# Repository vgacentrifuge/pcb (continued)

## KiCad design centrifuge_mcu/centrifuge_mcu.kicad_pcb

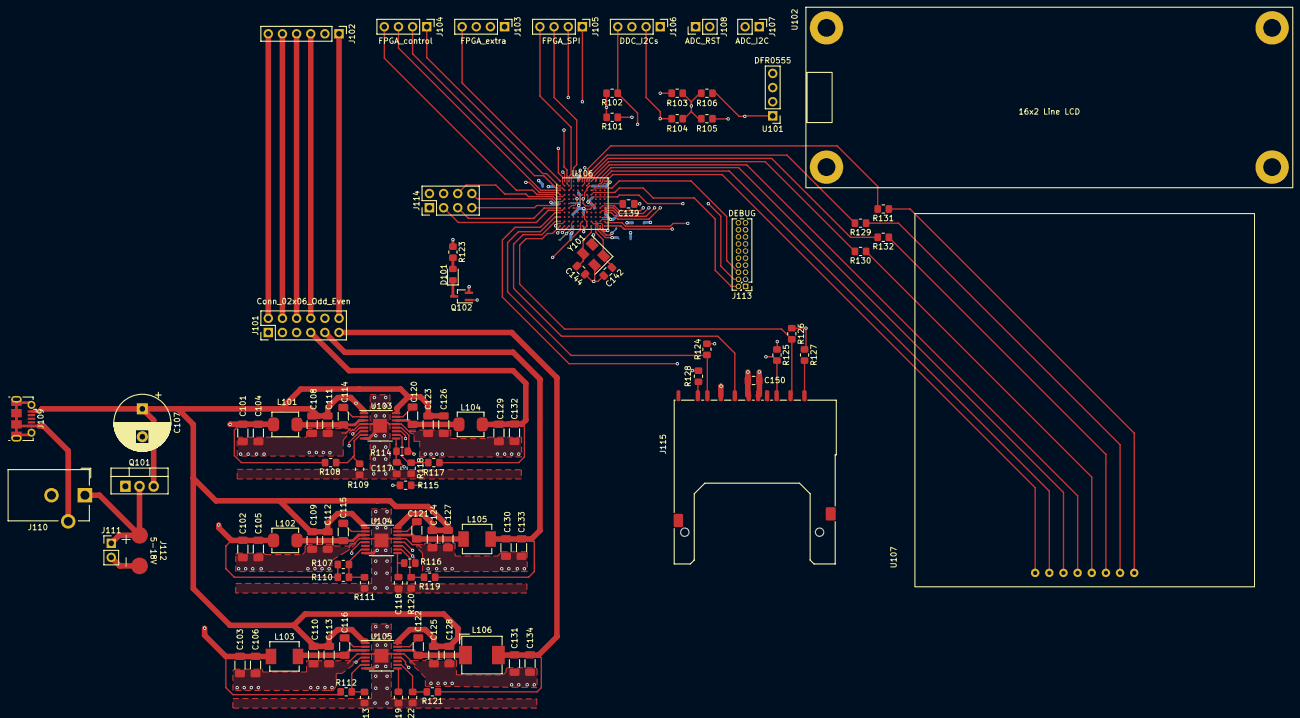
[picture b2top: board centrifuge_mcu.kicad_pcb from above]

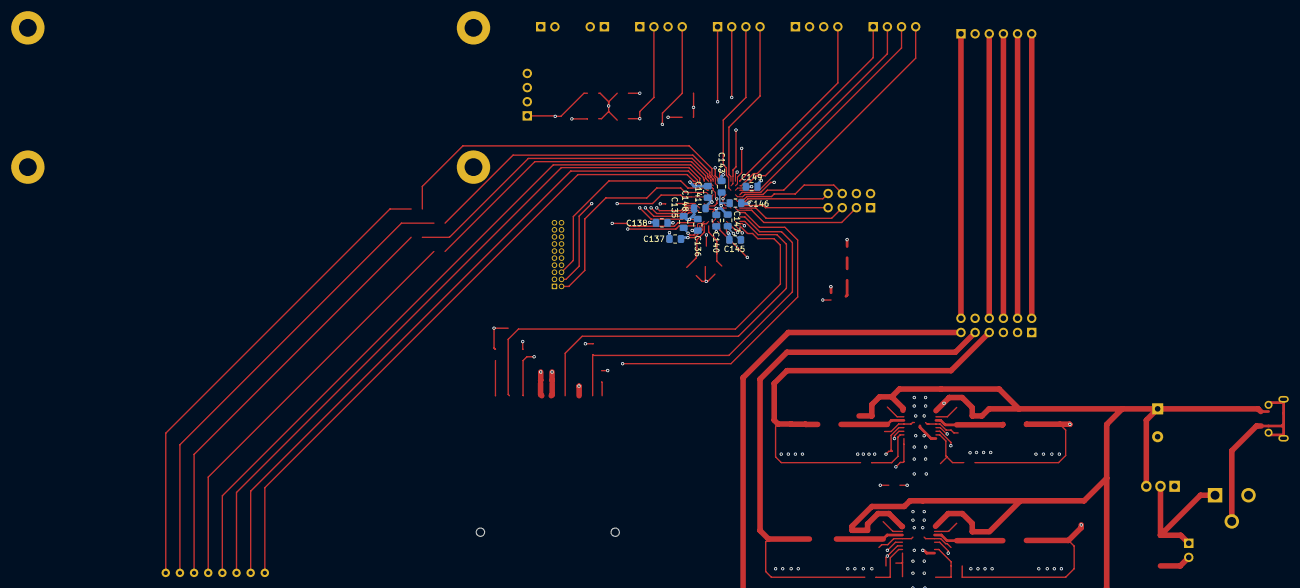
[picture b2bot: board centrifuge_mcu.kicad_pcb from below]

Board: 6 copper layers, 114 parts (12 on the bottom side), 94 nets.

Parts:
C101, C102, C103, C104, C105, C106, C129, C130, C131, C132, C133, C134: 22u; C_1206_3216Metric_Pad1.33x1.80mm_HandSolder
C107: 100u; CP_Radial_D10.0mm_P5.00mm
C108, C109, C110, C123, C124, C125: 10u; C_1206_3216Metric_Pad1.33x1.80mm_HandSolder
C111, C112, C113, C114, C115, C116, C120, C121, C122, C126, C127, C128: 100n; C_1206_3216Metric_Pad1.33x1.80mm_HandSolder
C117, C118, C119, C139: 1u; C_0805_2012Metric_Pad1.18x1.45mm_HandSolder
C135, C136, C137, C140, C141, C143, C145, C146, C147, C148, C150: 100n; C_0805_2012Metric_Pad1.18x1.45mm_HandSolder
C138, C149: 10u; C_0805_2012Metric_Pad1.18x1.45mm_HandSolder
C142, C144: 12p; C_0805_2012Metric_Pad1.18x1.45mm_HandSolder
D101: LED_YELLOW_2V_20mA; D_0805_2012Metric_Pad1.15x1.40mm_HandSolder
J101: Conn_02x06_Odd_Even; PinHeader_2x06_P2.54mm_Vertical
J102: FPGA_Power; PinHeader_1x06_P2.54mm_Vertical
J103: FPGA_extra; PinHeader_1x04_P2.54mm_Vertical
J104: FPGA_control; PinHeader_1x04_P2.54mm_Vertical
J105: FPGA_SPI; PinHeader_1x04_P2.54mm_Vertical
J106: DDC_I2Cs; PinHeader_1x04_P2.54mm_Vertical
J107: ADC_I2C; PinHeader_1x02_P2.54mm_Vertical
J108: ADC_RST; PinHeader_1x02_P2.54mm_Vertical
J109: USB_B_Micro; USB_Micro-B_Molex-105017-0001
J110: Barrel_Jack; BarrelJack_CUI_PJ-102AH_Horizontal
J111: PowerIn; PinHeader_1x02_P2.54mm_Vertical
J112: PowerPads
J113: DEBUG; PinHeader_2x10_P1.27mm_Vertical
J114: Extra MCU GPIO; PinHeader_2x04_P2.54mm_Vertical
J115: SD_Card; SD_Kyocera_145638009511859+
L101, L102, L104: 1.5u; L_Sumida_CR75
L103, L105: 2.2u; L_Vishay_IHLP-2020
L106: 3.3u; L_TDK_7065
Q101: Q_PMOS_DGS; TO-220-3_Vertical
Q102: Q_NMOS_GSD; SOT-323_SC-70_Handsoldering
R101, R102, R103, R104, R105, R106: 2.2k; R_0805_2012Metric_Pad1.20x1.40mm_HandSolder
R107: 5.6M; R_0805_2012Metric_Pad1.20x1.40mm_HandSolder
R108: 6.81k; R_0805_2012Metric_Pad1.20x1.40mm_HandSolder
R109, R111, R113, R118, R120, R122: 22.1k; R_0805_2012Metric_Pad1.20x1.40mm_HandSolder
R110: 33k; R_0805_2012Metric_Pad1.20x1.40mm_HandSolder
R112, R119: 73.2k; R_0805_2012Metric_Pad1.20x1.40mm_HandSolder
R114, R115, R116, R124, R125, R126, R127, R128, R129, R130, R131, R132: 10k; R_0805_2012Metric_Pad1.20x1.40mm_HandSolder
R117: 30.1k; R_0805_2012Metric_Pad1.20x1.40mm_HandSolder
R121: 124k; R_0805_2012Metric_Pad1.20x1.40mm_HandSolder
R123: 62; R_0805_2012Metric_Pad1.20x1.40mm_HandSolder
U101: DFR0555; PinHeader_1x04_P2.54mm_Vertical
U102: LCD16x2L; DFR0555
U103, U104, U105: TPS54294; TSSOP-16-1EP_4.4x5mm_P0.65mm_EP3x3mm_ThermalVias_EXTRA
U106: EFM32GG990F1024; BGA-112_9.0x9.0mm_Layout11x11_P0.8mm_Ball0.4mm_Pad0.35mm_NS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
U107: 4x4_keyboard; Adafruit 3844
Y101: VXM7-1366-48M0000000; Crystal_SMD_TXC_7M-4Pin_3.2x2.5mm_TIGHT

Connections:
+1V0: J101.6, J102.4
+1V8: J101.8, J102.3
+1V9: J101.4, J102.5
+3.3V: C135.1, C136.1, C137.1, C138.1, C140.1, C141.1, C143.1, C145.1, C146.1, C147.1, C148.1, C149.1, C150.2, J101.10, J102.2, J113.1, J114.1, J115.4 (VDD), R101.2, R102.2, R103.2, R104.2, R105.1, R106.1, R123.1, R124.2, R125.1, R126.1, R127.1, R128.2, U101.4 (VCC), U106.D5 (IOVDD_6), U106.D7 (IOVDD_5), U106.F8 (VDD_DREG), U106.G4 (IOVDD_0), U106.G8 (IOVDD_4), U106.H7 (IOVDD_3), U106.K8 (AVDD_2), U106.K9 (AVDD_1), U106.L4 (IOVDD_1), U106.L10 (AVDD_0)
+3.3VADC: J101.2, J102.6
+5V: J101.12, J102.1
/Button Panel/C0: U106.A11 (PF11), U107.1 (C0)
/Button Panel/C1: U106.B9 (PE5), U107.2 (C1)
/Button Panel/C2: U106.A10 (PF10), U107.3 (C2)
/Button Panel/C3: U106.A9 (PE4), U107.4 (C3)
/Button Panel/R0: R130.2, U106.A8 (PF12)
/Button Panel/R1: R132.2, U106.B7 (PF6)
/Button Panel/R2: R129.2, U106.A7 (PF5)
/Button Panel/R3: R131.2, U106.B6 (PF8)
/MCU/ADC0_RST: J108.1, U106.L11 (PD0)
/MCU/ADC1_RST: J108.2, U106.K11 (PD1)
/MCU/CMU_CLK#0: J104.4, U106.D2 (PA2/CMU_CLK0#0)
/MCU/FPGA_CONFIG_DONE: J104.1, U106.B1 (PA15)
/MCU/FPGA_INIT_B: J104.3, U106.C1 (PA1)
/MCU/FPGA_PROGRAM_B: J104.2, U106.C2 (PA0)
/MCU/I2C0_SCL#1: J106.2, R104.1, U106.H11 (PD7/I2C0_SCL#1)
/MCU/I2C0_SCL#2: J106.4, R102.1, U106.G11 (PC7/I2C0_SCL#2)
/MCU/I2C0_SDA#1: J106.1, R103.1, U106.H10 (PD6/I2C0_SDA#1)
/MCU/I2C0_SDA#2: J106.3, R101.1, U106.G10 (PC6/I2C0_SDA#2)
/MCU/I2C1_SCL: J107.2, R105.2, U101.2 (SCL), U106.L2 (PC5/I2C1_SCL#0)
/MCU/I2C1_SDA: J107.1, R106.2, U101.1 (SDA), U106.K2 (PC4/I2C1_SDA#0)
/MCU/MF-IO0: J103.1, U106.A6 (PF7)
/MCU/MF-IO1: J103.2, U106.A5 (PD10)
/MCU/MF-IO2: J103.3, U106.A2 (PE14)
/MCU/MF-IO3: J103.4, U106.A1 (PE15)
/MCU/SPI0_CLK: J105.4, U106.A3 (PE12/US0_CLK#0)
/MCU/SPI0_CS: J105.1, U106.B2 (PE13/US0_CS#0)
/MCU/SPI0_MISO: J105.2, U106.B3 (PE11/US0_RX#0)
/MCU/SPI0_MOSI: J105.3, U106.C3 (PE10/US0_TX#0)
/MCU/SPI1_CLK: J115.5 (CLK), U106.K1 (PB7/US1_CLK#0)
/MCU/SPI1_CS: J115.1 (CD/DAT3), R126.2, U106.L1 (PB8/US1_CS#0)
/MCU/SPI1_MISO: J115.7 (DAT0), R124.1, U106.J1 (PC1/US1_RX#0)
/MCU/SPI1_MOSI: J115.2 (CMD), R125.2, U106.H1 (PC0/US1_TX#0)
/Power Circuit/1V0: C101.1, C104.1, J101.5, L101.1, R108.1
/Power Circuit/1V8: C129.1, C132.1, J101.7, L104.2, R117.1
/Power Circuit/1V9: C102.1, C105.1, J101.3, L102.1, R107.1, R110.1
/Power Circuit/3V3: C130.1, C133.1, J101.9, L105.2, R119.1
/Power Circuit/3V3ADC: C103.1, C106.1, J101.1, L103.1, R112.1
/Power Circuit/5V0: C131.1, C134.1, J101.11, L106.2, R121.1
GND: C101.2, C102.2, C103.2, C104.2, C105.2, C106.2, C107.2, C108.2, C109.2, C110.2, C111.2, C112.2, C113.2, C117.1, C118.1, C119.1, C123.2, C124.2, C125.2, C126.2, C127.2, C128.2, C129.2, C130.2, C131.2, C132.2, C133.2, C134.2, C135.2, C136.2, C137.2, C138.2, C139.1, C140.2, C141.2, C142.2, C143.2, C144.2, C145.2, C146.2, C147.2, C148.2, C149.2, C150.1, J110.2, J111.2, J112.2, J113.3, J113.5, J113.9, J113.11, J113.13, J113.15, J113.17, J113.19, J114.2, J115.3 (VSS), J115.6 (VSS), Q101.1 (G), Q102.2 (S), R109.2, R111.2, R113.2, R118.2, R120.2, R122.2, U101.3 (GND), U103.4 (PGND1), U103.8 (GND), U103.13 (PGND2), U103.17 (PwPd), U104.4 (PGND1), U104.8 (GND), U104.13 (PGND2), U104.17 (PwPd), U105.4 (PGND1), U105.8 (GND), U105.13 (PGND2), U105.17 (PwPd), U106.B8 (USB_VBUS), U106.B10 (USB_VREGI), U106.C7 (VSS), U106.D4 (VSS), U106.F9 (VSS_DREG), U106.G3 (VSS), U106.G9 (VSS), U106.H6 (VSS), U106.K4 (VSS), U106.K7 (AVSS_1), U106.K10 (AVSS_0), U106.L7 (AVSS_2), Y101.2, Y101.4
unnamed: C107.1, C108.1, C109.1, C110.1, C111.1, C112.1, C113.1, C123.1, C124.1, C125.1, C126.1, C127.1, C128.1, J109.1 (VBUS), Q101.3 (S), U103.1 (VIN1), U103.5 (EN1), U103.16 (VIN2), U104.1 (VIN1), U104.16 (VIN2), U105.1 (VIN1), U105.16 (VIN2)
unnamed: C114.1, U103.2 (VBST1)
unnamed: C114.2, L101.2, U103.3 (SW1)
unnamed: C115.1, U104.2 (VBST1)
unnamed: C115.2, L102.2, U104.3 (SW1)
unnamed: C116.1, U105.2 (VBST1)
unnamed: C116.2, L103.2, U105.3 (SW1)
unnamed: C117.2, R114.1, R115.1, U103.9 (VREG5)
unnamed: C118.2, R116.1, U104.9 (VREG5)
unnamed: C119.2, U105.9 (VREG5)
unnamed: C120.1, U103.15 (VBST2)
unnamed: C120.2, L104.1, U103.14 (SW2)
unnamed: C121.1, U104.15 (VBST2)
unnamed: C121.2, L105.1, U104.14 (SW2)
unnamed: C122.1, U105.15 (VBST2)
unnamed: C122.2, L106.1, U105.14 (SW2)
unnamed: C139.2, U106.F11 (DECOUPLE)
unnamed: C142.1, U106.L9 (PB14/HFXTAL_N), Y101.1
unnamed: C144.1, U106.L8 (PB13/HFXTAL_P), Y101.3
unnamed: D101.1 (K), Q102.3 (D)
unnamed: D101.2 (A), R123.2
unnamed: J109.5 (GND), J109.6 (Shield), J110.3
unnamed: J110.1, J111.1, J112.1, Q101.2 (D)
unnamed: J113.2, U106.D8 (DBG_SWDIO#0)
unnamed: J113.4, U106.E8 (DBG_SWCLK#0)
unnamed: J113.6, U106.C8 (DBG_SWO#0)
unnamed: J113.10, U106.K6 (~RESET)
unnamed: J114.3, U106.G2 (PB6)
unnamed: J114.4, U106.D1 (PA3)
unnamed: J114.5, U106.G1 (PB5)
unnamed: J114.6, U106.E1 (PA6)
unnamed: J114.7, U106.F1 (PB1)
unnamed: J114.8, U106.E2 (PA5)
unnamed: J115.8 (DAT1), R128.1
unnamed: J115.9 (DAT2), R127.2
unnamed: Q102.1 (G), U106.L3 (PA14)
unnamed: R107.2, R110.2, R111.1, U104.7 (VFB1)
unnamed: R108.2, R109.1, U103.7 (VFB1)
unnamed: R112.2, R113.1, U105.7 (VFB1)
unnamed: R114.2, U103.6 (PG1), U103.12 (EN2)
unnamed: R115.2, U103.11 (PG2), U104.12 (EN2)
unnamed: R116.2, U104.5 (EN1), U104.11 (PG2), U105.5 (EN1), U105.12 (EN2)
unnamed: R117.2, R118.1, U103.10 (VFB2)
unnamed: R119.2, R120.1, U104.10 (VFB2)
unnamed: R121.2, R122.1, U105.10 (VFB2)
unnamed: R129.1, U107.7 (R2)
unnamed: R130.1, U107.5 (R0)
unnamed: R131.1, U107.8 (R3)
unnamed: R132.1, U107.6 (R1)

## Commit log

2022-09-10 start on README, details about the design
2022-09-10 write about DAC and ADC, we should get to ordering those
2022-09-11 write about VGA DDC, I2C and stuff
2022-09-11 try finding components for the PCB and development
2022-09-12 Started DRAM-FPGA schematic and outline of rest
2022-09-12 write about SRAM chip and timing, as well as add some SD card over SPI links
2022-09-14 add manual for the SRAM chip
2022-09-14 replace SRAM with another, synchronous SRAM chip
2022-09-14 mention JTAG for the SRAM
2022-09-14 add note about I2C voltage, and link to ADC
2022-09-15 start on shopping list, and improve readme in places
2022-09-15 add more items to the shopping list
2022-09-15 add shopping list with all main components, look at a bunch of support components
2022-09-16 Implemented DRAM connections
2022-09-16 add level shifters for I2C, H/V-SYNC and MCU clock to shopping list
2022-09-16 add some connectors to the shopping list
2022-09-17 block diagram with dram
2022-09-17 removed DRAM from block diagram, added TVS protection where necessary
2022-09-17 Made initial pin map of SRAM-FPGA and possible routing
2022-09-21 Completed majority of schematic, need to add decoupling but otherwise mostly ready
2022-09-30 FPGA PCB design completed
2022-10-01 more footprints, add links to resistor and inductance purchase
2022-10-01 make and pick footprints for almost everything
2022-10-01 finish main component shopping list
2022-10-01 continue on power supply routing
2022-10-01 add some connectors, the config flash, and I2C mosfets to the shopping list
2022-10-01 add clock oscillator to shopping list
2022-10-01 work on MCU schematic
2022-10-01 replace all level switches with a single cheap one
2022-10-01 change I2C level switch on shopping list
2022-10-01 last footprints, time to route (after final FPGA-board connectors)
2022-10-01 slowly but surely decopling and connecting everything to the MCU
2022-10-01 start routing PCB for the MCU, starting with power
2022-10-01 hooking things up to the MCU, maybe we could even make the board a bit smaller
2022-10-01 do all MCU I think I can before merging in FPGA PCB
2022-10-01 rebase with FPGA pcb, trying to add it
2022-10-02 connect everything in MCU pcb, connection time
2022-10-02 Draft merged PCB
2022-10-02 Almost finished releasable version
2022-10-03 Board appears ok
2022-10-03 fixed keypad hole sizes, and submitted
2022-10-03 create new PSU routing for all 6 voltages
2022-10-03 Fixed missing footprints, added decoupling capacitors, adjusted board edges
2022-10-03 Fixed up schematic names and page numbers
2022-10-03 Improved PCB manufacturing tolerances
2022-10-03 Updated zone fills
2022-10-04 remove backup files from the repository
2022-10-04 remove digikey links to products that we already buy from mouser, add mouser link instead
2022-10-05 do double checks, and fix link in README. Pre elprint-fixup
2022-10-05 fix elprint complaints, except intranet clearance, also widen some traces
2022-10-05 add a little logo to the corner
2022-10-05 try to improve clearances, not sure where the complaints are
2022-10-05 more checks, also make silkscreen text for connectors
2022-10-05 fix JTAG Vref, pullup on CS and remove SRAM_CS1p3
2022-10-05 Fixed Elprint complaints and JTAG VREF problems+config flash CS
2022-10-05 make some power traces thicker
2022-10-06 fix elprint same_net complaints, I hope
2022-10-06 HANDIN: do final pcb trace niceness
2022-10-11 add pcb overview diagram
2022-10-12 start on shopping list 2
2022-10-13 make final shopping list, added to Mouser and DigiKey lists. Also budget. Swaps out TVS diodes
2022-10-13 fix duplicate Cs, add extra ACD/DAC and breakout, and fix TVS schematic hidden pin
2022-10-13 export DigiKey and Mouser lists to excel. Add extra to DigiKey where cheaper
2022-10-18 add spreadsheet for actual choices of I2C resistors
2022-10-22 change resistor values to have to 2k2, and also make I2C hopefully work
2022-10-28 change the names of some named wires in the schematic, to make numbering more consistent
2022-10-28 add shopping list for last batch of missing capacitors
2022-11-03 fix mismatch between VSYNC and HSYNC out, only needs a swap in constraints file as well
2022-11-03 also reimport schematic into pcb, no differences
2022-11-09 fully commit to calling top VGA ADC2
2022-11-12 add note about changes to VGA0's I2C stuff
